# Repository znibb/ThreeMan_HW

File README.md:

# ThreeMan_HW

## Description
PCB design for the ThreeMan dice game (see [ThreeMan](https://github.com/znibb/ThreeMan)).

|  |  |
| --- | --- |

## Changelog
The format is based on [Keep a Changelog](https://keepachangelog.com/).  

According to Hardware Semantic Versioning (MAJOR.MINOR.PATCH), increment:
* MAJOR - when changing mechanical or connector interfaces
* MINOR - when changing schematic or layout
* PATCH - when changing BOM or sourcing data

All notable changes to this PCB project will be documented in [CHANGELOG.md](CHANGELOG.md).

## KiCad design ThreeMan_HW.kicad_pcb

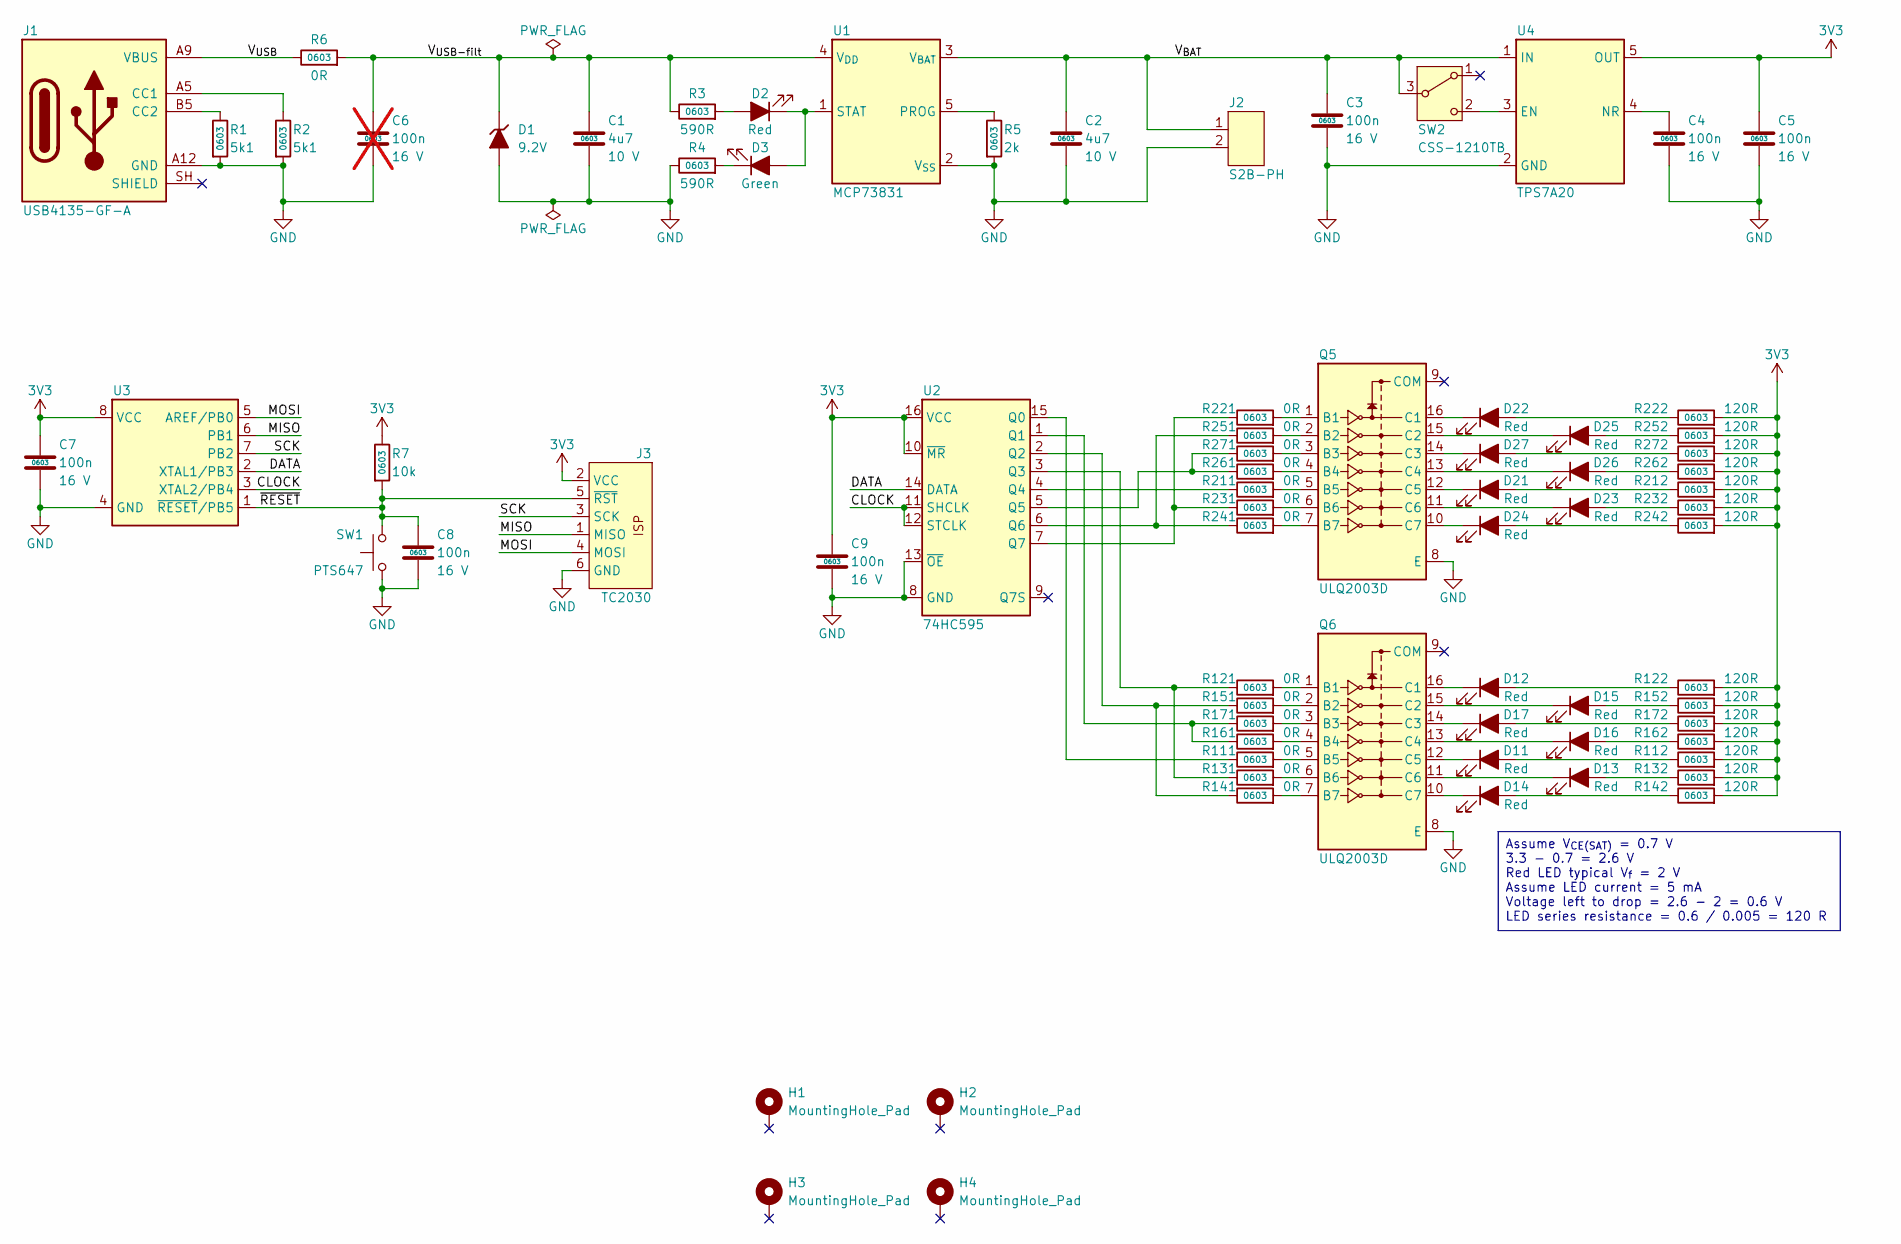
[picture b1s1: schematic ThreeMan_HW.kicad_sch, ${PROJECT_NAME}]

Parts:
C1, C2: 4u7; C_0603_1608Metric; VoltageRating 10 V; Tolerance 20 %; MPN CC0603MRX5R6BB475
C3, C4, C5, C7, C8, C9: 100n; C_0603_1608Metric; VoltageRating 16 V; Tolerance 10 %; MPN CC0603KRX7R7BB104
C6: 100n; C_0603_1608Metric; VoltageRating 16 V; Tolerance 10 %; MPN CC0603KRX7R7BB104; not fitted
D1: 9.2V; D_SMA; VoltageBreakdown 6.4 V; VoltageClamping 9.2 V; MPN SMAJ5.0A
D2, D11, D12, D13, D14, D15, D16, D17, D21, D22, D23, D24, D25, D26, D27: LTST-C191KRKT; LED_0603_1608Metric; VoltageForward 2 V; MPN LTST-C191KRKT
D3: LTST-C190KGKT[A; LED_0603_1608Metric; VoltageForward 2.1 V; MPN LTST-C190KGKT[A
H1, H2, H3, H4: MountingHole_Pad; MountingHole_3.2mm_Pad
J1: USB4135-GF-A; GCT-USB4135-GF-A; VoltageRating 48 V; MPN USB4135-GF-A
J2: S2B-PH; JST_PH_B2B-PH-SM4-TB_1x02-1MP_P2.00mm_Vertical; MPN S2B-PH-SM4-TB
J3: TC2030; TagConnect_TC2030_2x3_DualSide
Q5, Q6: ULQ2003D; SOIC-16_3.9x9.9mm_P1.27mm; VoltageCollectorEmitter 50 V; MPN ULQ2003D1013TRY
R1, R2: 5k1; R_0603_1608Metric; Tolerance 1 %; MPN RC0603FR-075K1L
R3, R4: 590R; R_0603_1608Metric; Tolerance 1 %; MPN RC0603FR-13590RL
R5: 2k; R_0603_1608Metric; Tolerance 1 %; MPN RC0603FR-102KL
R6, R111, R121, R131, R141, R151, R161, R171, R211, R221, R231, R241, R251, R261, R271: 0R; R_0603_1608Metric; Tolerance %; MPN RC0603JR-070RL
R7: 10k; R_0603_1608Metric; Tolerance 1 %; MPN RC0603FR-0710KL
R112, R122, R132, R142, R152, R162, R172, R212, R222, R232, R242, R252, R262, R272: 120R; R_0603_1608Metric; Tolerance 1 %; MPN RC0603FR-07120RL
SW1: PTS647; SW_Push_SPST_4.5x4.5mm_H7.0mm; VoltageRating 12 V; MPN PTS647SM70SMTR2 LFS
SW2: CSS-1210TB; VoltageRating 12 V; MPN CSS-1210TB
U1: MCP73831; SOT-23-5; MPN MCP73831T-2ACI-OT
U2: 74HC595; TSSOP-16_4.4x5mm_P0.65mm; MPN 74HC595PW,118
U3: ATTINY85; SOIC-8_5.3x5.3mm_P1.27mm; MPN ATTINY85-20SUR
U4: TPS7A20; SOT-23-5; MPN TPS7A2033PDBVR

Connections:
/3V3: C5.1, C7.1, C9.1, J3.2 (VCC), R7.1, R112.2, R122.2, R132.2, R142.2, R152.2, R162.2, R172.2, R212.2, R222.2, R232.2, R242.2, R252.2, R262.2, R272.2, U2.10 (~MR), U2.16 (VCC), U3.8 (VCC), U4.5 (OUT)
/CLOCK: U2.11 (SHCLK), U2.12 (STCLK), U3.3 (XTAL2/PB4)
/DATA: U2.14 (DATA), U3.2 (XTAL1/PB3)
/GND: C1.2, C2.2, C3.2, C4.2, C5.2, C6.2, C7.2, C8.2, C9.2, D1.2, J1.A12 (GND), J1.B12 (GND), J2.2, J3.6 (GND), Q5.8 (E), Q6.8 (E), R1.2, R2.2, R4.1, R5.2, SW1.1, U1.2 (V_{SS}), U2.8 (GND), U2.13 (~OE), U3.4 (GND), U4.2 (GND)
/MISO: J3.1 (MISO), U3.6 (PB1)
/MOSI: J3.4 (MOSI), U3.5 (AREF/PB0)
/SCK: J3.3 (SCK), U3.7 (PB2)
/V_{BAT}: C2.1, C3.1, J2.1, SW2.3 (B), U1.3 (V_{BAT}), U4.1 (IN)
/V_{USB-filt}: C1.1, C6.1, D1.1, R3.1, R6.2, U1.4 (V_{DD})
/V_{USB}: J1.A9 (VBUS), J1.B9 (VBUS), R6.1
/~RESET: C8.1, J3.5 (~RST), R7.2, SW1.2, U3.1 (~RESET/PB5)
unnamed: D2.A, R3.2
unnamed: D3.C, R4.2
unnamed: D11.A, R112.1
unnamed: D12.A, R122.1
unnamed: D13.A, R132.1
unnamed: D14.A, R142.1
unnamed: D15.A, R152.1
unnamed: D16.A, R162.1
unnamed: D17.A, R172.1
unnamed: D21.A, R212.1
unnamed: D22.A, R222.1
unnamed: D23.A, R232.1
unnamed: D24.A, R242.1
unnamed: D25.A, R252.1
unnamed: D26.A, R262.1
unnamed: D27.A, R272.1
unnamed: J1.A5 (CC1), R2.1
unnamed: J1.B5 (CC2), R1.1
unnamed: Q5.1 (B1), R221.2
unnamed: Q5.2 (B2), R251.2
unnamed: Q5.3 (B3), R271.2
unnamed: Q5.4 (B4), R261.2
unnamed: Q5.5 (B5), R211.2
unnamed: Q5.6 (B6), R231.2
unnamed: Q5.7 (B7), R241.2
unnamed: D22.C, Q5.16 (C1)
unnamed: D25.C, Q5.15 (C2)
unnamed: D27.C, Q5.14 (C3)
unnamed: D26.C, Q5.13 (C4)
unnamed: D21.C, Q5.12 (C5)
unnamed: D23.C, Q5.11 (C6)
unnamed: D24.C, Q5.10 (C7)
unnamed: Q6.1 (B1), R121.2
unnamed: Q6.2 (B2), R151.2
unnamed: Q6.3 (B3), R171.2
unnamed: Q6.4 (B4), R161.2
unnamed: Q6.5 (B5), R111.2
unnamed: Q6.6 (B6), R131.2
unnamed: Q6.7 (B7), R141.2
unnamed: D12.C, Q6.16 (C1)
unnamed: D15.C, Q6.15 (C2)
unnamed: D17.C, Q6.14 (C3)
unnamed: D16.C, Q6.13 (C4)
unnamed: D11.C, Q6.12 (C5)
unnamed: D13.C, Q6.11 (C6)
unnamed: D14.C, Q6.10 (C7)
unnamed: SW2.2 (C), U4.3 (EN)
unnamed: R5.1, U1.5 (PROG)
unnamed: D2.C, D3.A, U1.1 (STAT)
unnamed: R111.1, U2.15 (Q0)
unnamed: R161.1, R171.1, U2.1 (Q1)
unnamed: R141.1, R151.1, U2.2 (Q2)
unnamed: R121.1, R131.1, U2.3 (Q3)
unnamed: R211.1, U2.4 (Q4)
unnamed: R261.1, R271.1, U2.5 (Q5)
unnamed: R241.1, R251.1, U2.6 (Q6)
unnamed: R221.1, R231.1, U2.7 (Q7)
unnamed: C4.1, U4.4 (NR)

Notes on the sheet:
Assume V_{CE(SAT)} = 0.7 V 3.3 - 0.7 = 2.6 V Red LED typical V_{f} = 2 V Assume LED current = 5 mA Voltage left to drop = 2.6 - 2 = 0.6 V LED series resistance = 0.6 / 0.005 = 120 R

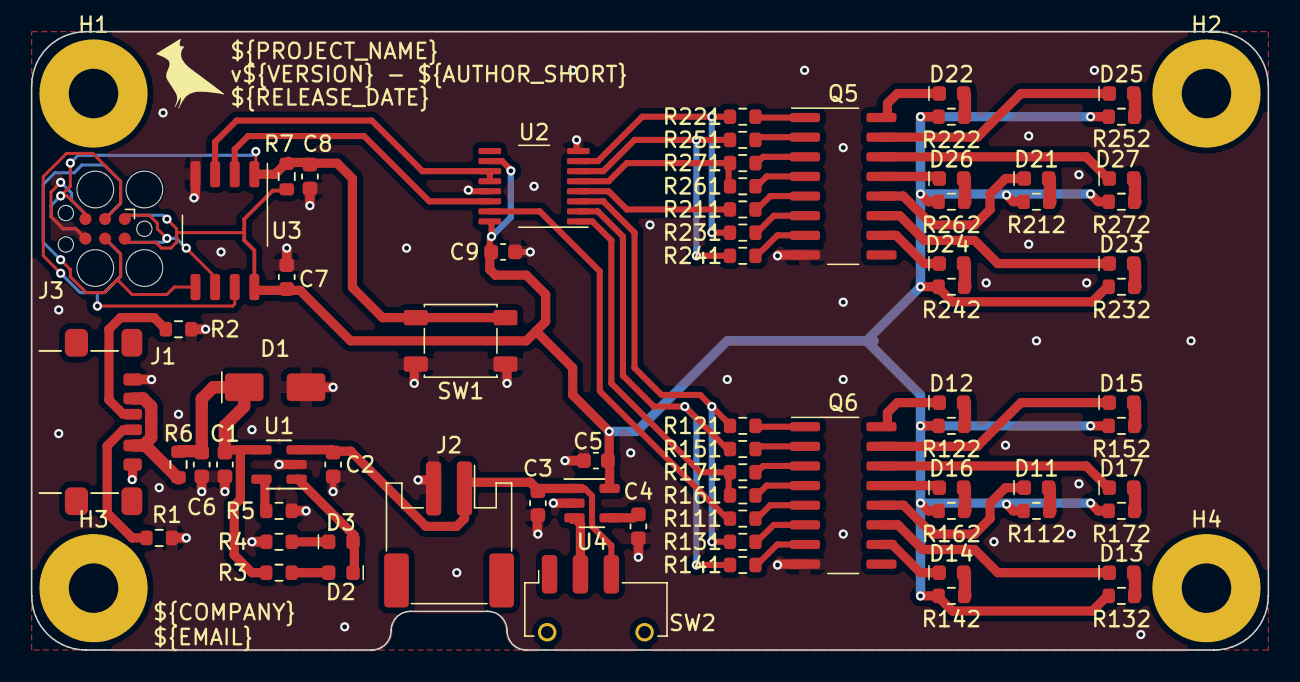
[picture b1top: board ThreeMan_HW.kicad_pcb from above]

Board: 4 copper layers, 80.0 x 40.0 mm, 76 parts (0 on the bottom side), 69 nets.

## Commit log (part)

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2023-04-27 Added backup files to .gitignore
2024-08-26 Added lock files to .gitignore
2024-08-26 Imported updated schematic drawing
2024-08-27 Finished initial draft of A1 schematic and imported it to PCB
2025-05-20 Completed layout
